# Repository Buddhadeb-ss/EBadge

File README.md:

<br>

# EBadge

## Overview

Official repository for the Point Blank Club Electronic Badge (EBadge). This project contains all hardware files, 3D printable enclosure designs, documentation, and firmware required to build and program your own feature-packed electronic event badge.

---

## Features

* **Interactive Display & Menu System:** Custom UI driven by dedicated display code.
* **On-Badge Games:**
  * **Dino Game:** Classic side-scrolling obstacle jump game.
  * **Flappy Game:** Flappy Bird style arcade game.
* **Web Portal Interface:** Onboard Wi-Fi web portal for setup and customization.
* **Local Storage Support:** Persistent saving for preferences, high scores, and settings.
* **Tactile Controls:** Dedicated button engine for responsive navigation and gameplay.
* **Custom Hardware & Enclosure:** Complete KiCad PCB design, gerber files, BOM, and 3D printable STL enclosure models.

---

## Repository Structure

```text
EBadge/
├── assets/             # Branding assets and graphics
├── docs/               # Detailed guides and project documentation
│   ├── GUIDE.md        # Development, setup and firmware guide
│   ├── CONTRIBUTING.md # Contribution workflow and guidelines
│   ├── ISSUES.md       # Guide for reporting bugs and problems
│   ├── FUTURE_FEATURES.md # Prioritised software feature backlog
│   └── Images/         # Documentation screenshots and visual aids
├── enclosure/          # 3D printable files & enclosure visuals
│   ├── Images/         # Photos/renders of the assembled badge
│   └── STL/            # 3D printable STL models
├── firmware/           # Microcontroller source code
│   └── eBadge/         # Main firmware code directory
│       ├── eBadge.ino  # Main entry sketch
│       ├── menu.*      # UI & menu engine
│       ├── webportal.* # Web interface module
│       ├── display.*   # Display driver code
│       ├── buttons.*   # Button input handler
│       ├── storage.*   # Non-volatile memory controller
│       ├── dinogame.*  # Dino game module
│       └── flappygame.*# Flappy game module
└── hardware/           # Hardware and circuit design files
    ├── BOM/            # Bill of Materials
    ├── datasheets/     # Component datasheets
    ├── gerbers/        # Production-ready PCB Gerber files
    └── kicad/          # KiCad EDA source files
```

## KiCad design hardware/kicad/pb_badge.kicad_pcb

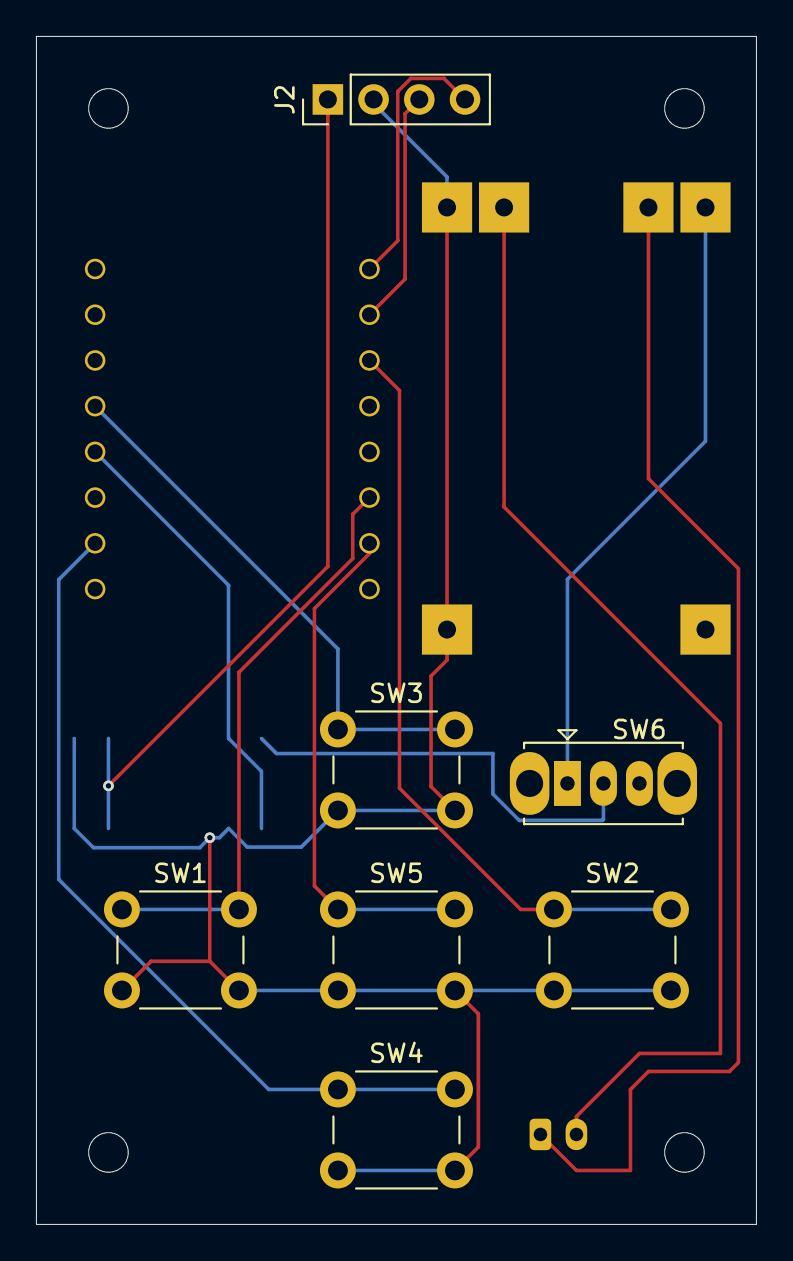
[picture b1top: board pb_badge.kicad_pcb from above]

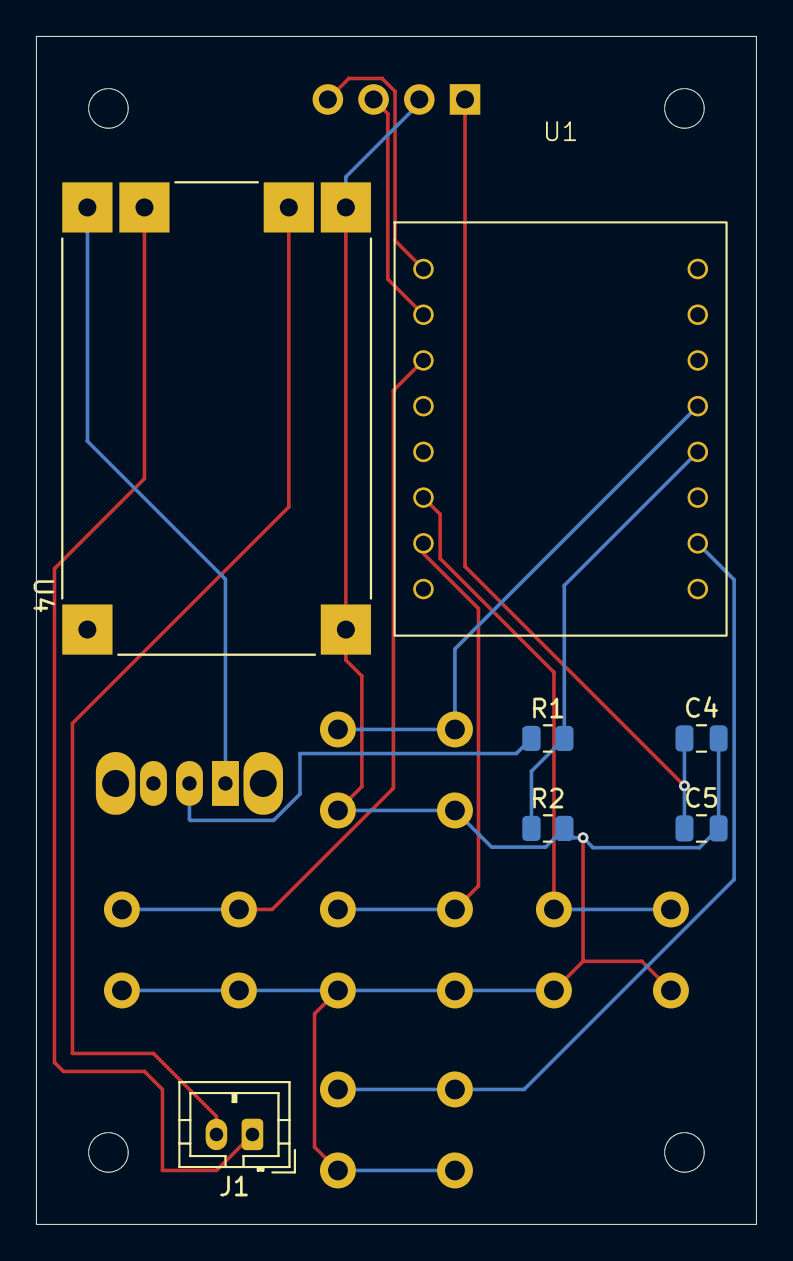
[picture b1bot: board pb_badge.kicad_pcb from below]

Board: 2 copper layers, 40.0 x 66.0 mm, 14 parts (7 on the bottom side), 14 nets.

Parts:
C4, C5: 100nF; C_0805_2012Metric
J1: Conn_01x02_Pin; JST_PH_B2B-PH-K_1x02_P2.00mm_Vertical
J2: SSD1306_OLED; PinHeader_1x04_P2.54mm_Vertical
R1, R2: 10k; R_0805_2012Metric
SW1, SW2, SW3, SW4, SW5: SW_Push; SW_PUSH_6mm_H5mm
SW6: SW_SPST; SW_Slide_SPDT_Straight_CK_OS102011MS2Q
U1: ESP32-C3-SuperMini
U4: TP4056_MICRO-USB_CHARGER_-_1A; MODULE_TP4056_MICRO-USB_CHARGER_-_1A

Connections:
+3v3: C4.1, C5.1, J2.1
GND: C4.2, C5.2, J2.2, R2.2, SW1.2, SW2.2, SW3.2, SW4.2, SW5.2, U4.IN_N (IN-), U4.OUT_N (OUT-)
unnamed: J1.1, U4.BAT_P (BAT+)
unnamed: J1.2, U4.BAT_N (BAT-)
unnamed: SW6.1 (A), U4.OUT_P (OUT+)
btn_a: SW1.1, U1.10 (GPIO10)
btn_b: SW2.1, U1.7 (GPIO7)
btn_dwn: SW4.1, U1.1 (GPIO1)
btn_menu: SW5.1, U1.20 (GPIO20)
btn_up: SW3.1, U1.4 (GPIO4)
scl: J2.3, U1.6 (GPIO6)
sda: J2.4, U1.5 (GPIO5)
vbat_sense: R1.2, R2.1, U1.3 (GPIO3)
vbat_sw: R1.1, SW6.2 (B)
